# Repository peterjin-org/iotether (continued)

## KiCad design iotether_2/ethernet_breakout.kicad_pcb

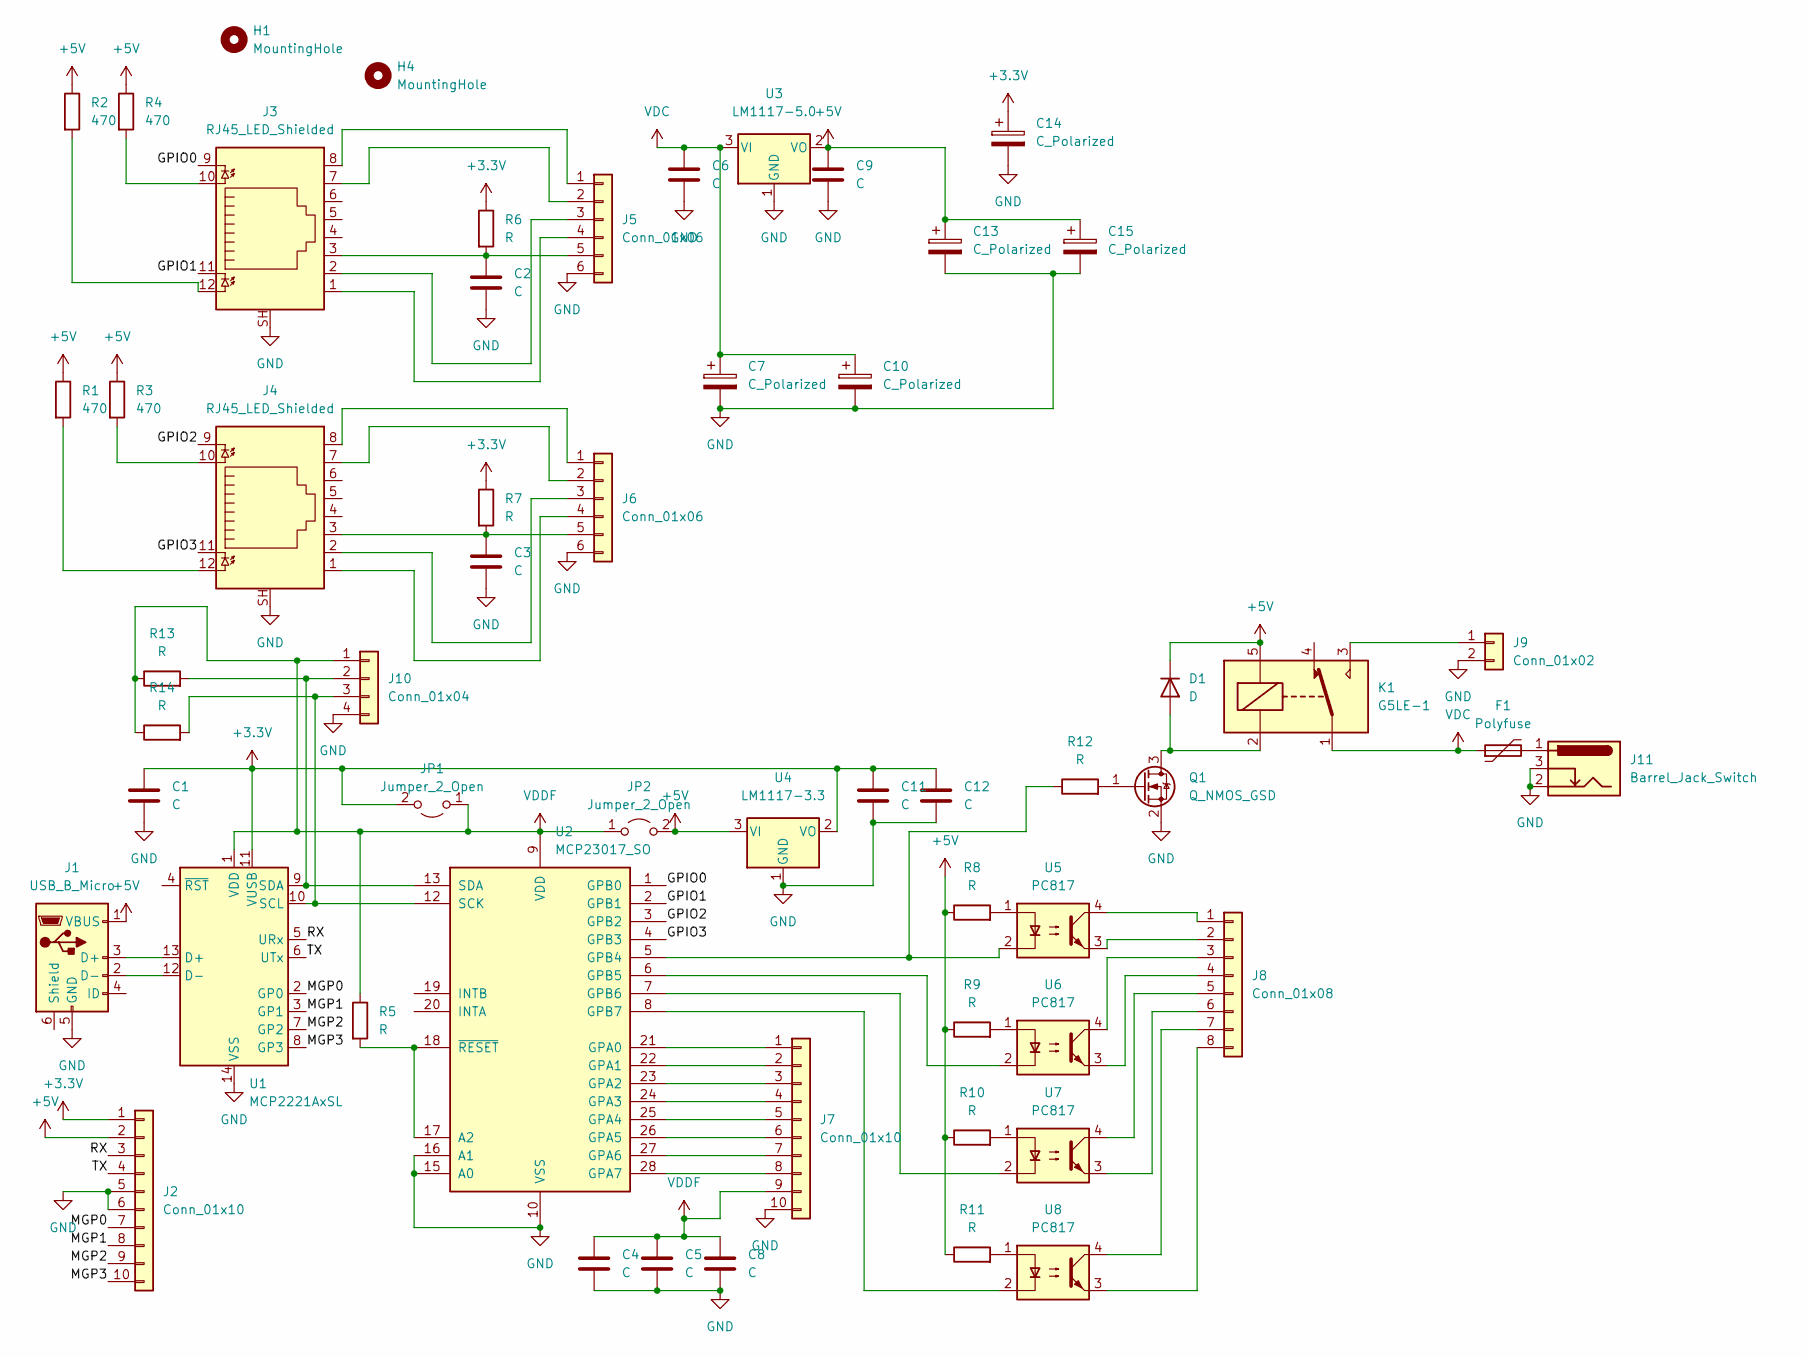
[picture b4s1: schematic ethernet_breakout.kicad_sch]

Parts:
C1, C2, C3, C4, C5, C6, C8, C9, C11, C12: C; C_0603_1608Metric_Pad1.08x0.95mm_HandSolder
C7, C10, C13, C14, C15: C_Polarized; CP_Radial_D8.0mm_P3.50mm
D1: D; D_DO-41_SOD81_P3.81mm_Vertical_AnodeUp
F1: Polyfuse; Fuse_Bourns_MF-RHT500
H1, H4: MountingHole; MountingHole_3.2mm_M3
J1: USB_B_Micro; PinHeader_1x06_P2.54mm_Vertical
J2, J7: Conn_01x10; PinHeader_1x10_P2.54mm_Vertical
J3, J4: RJ45_LED_Shielded; RJ45_Cetus_J1B1211CCD_Horizontal
J5, J6: Conn_01x06; PinHeader_1x06_P2.54mm_Vertical
J8: Conn_01x08; PinHeader_2x04_P2.54mm_Vertical
J9: Conn_01x02; TerminalBlock_bornier-2_P5.08mm
J10: Conn_01x04; PinHeader_1x04_P2.54mm_Vertical
J11: Barrel_Jack_Switch; BarrelJack_Horizontal
JP1, JP2: Jumper_2_Open; R_0603_1608Metric_Pad0.98x0.95mm_HandSolder
K1: G5LE-1; Relay_SPDT_Omron-G5LE-1
Q1: Q_NMOS_GSD; SOT-23-3
R1, R2, R3, R4: 470; R_0603_1608Metric
R5, R6, R7, R8, R9, R10, R11, R12, R13, R14: R; R_0603_1608Metric_Pad0.98x0.95mm_HandSolder
U1: MCP2221AxSL; SOIC-14_3.9x8.7mm_P1.27mm
U2: MCP23017_SO; SOIC-28W_7.5x17.9mm_P1.27mm
U3: LM1117-5.0; SOT-223-3_TabPin2
U4: LM1117-3.3; SOT-223-3_TabPin2
U5, U6, U7, U8: PC817; DIP-4_W7.62mm

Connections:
+3.3V: C1.1, C11.1, C12.1, C14.1, J2.1, JP1.2 (B), R6.1, R7.1, U1.11 (VUSB), U4.2 (VO)
+5V: C9.1, C13.1, C15.1, D1.1 (K), J1.1 (VBUS), J2.2, JP2.2 (B), K1.5, R1.1, R2.1, R3.1, R4.1, R8.1, R9.1, R10.1, R11.1, U3.2 (VO), U4.3 (VI)
/GPIO0: J3.9, U2.1 (GPB0)
/GPIO1: J3.11, U2.2 (GPB1)
/GPIO2: J4.9, U2.3 (GPB2)
/GPIO3: J4.11, U2.4 (GPB3)
/MGP0: J2.7, U1.2 (GP0)
/MGP1: J2.8, U1.3 (GP1)
/MGP2: J2.9, U1.7 (GP2)
/MGP3: J2.10, U1.8 (GP3)
/RX: J2.3, U1.5 (URx)
/TX: J2.4, U1.6 (UTx)
GND: C1.2, C2.2, C3.2, C4.2, C5.2, C6.2, C7.2, C8.2, C9.2, C10.2, C11.2, C12.2, C13.2, C14.2, C15.2, J1.5 (GND), J2.5, J2.6, J3.SH, J4.SH, J5.6, J6.6, J7.10, J9.2, J10.4, J11.2, J11.3, Q1.2 (S), U1.14 (VSS), U2.10 (VSS), U2.15 (A0), U2.16 (A1), U3.1 (GND), U4.1 (GND)
unnamed: C2.1, J3.3, J5.5, R6.2
unnamed: C3.1, J4.3, J6.5, R7.2
unnamed: D1.2 (A), K1.2, Q1.3 (D)
unnamed: J1.2 (D-), U1.12 (D-)
unnamed: J1.3 (D+), U1.13 (D+)
unnamed: J3.1, J5.4
unnamed: J3.2, J5.3
unnamed: J3.7, J5.2
unnamed: J3.8, J5.1
unnamed: J3.10, R4.2
unnamed: J3.12, R2.2
unnamed: J4.1, J6.4
unnamed: J4.2, J6.3
unnamed: J4.7, J6.2
unnamed: J4.8, J6.1
unnamed: J4.10, R3.2
unnamed: J4.12, R1.2
unnamed: J7.1, U2.21 (GPA0)
unnamed: J7.2, U2.22 (GPA1)
unnamed: J7.3, U2.23 (GPA2)
unnamed: J7.4, U2.24 (GPA3)
unnamed: J7.5, U2.25 (GPA4)
unnamed: J7.6, U2.26 (GPA5)
unnamed: J7.7, U2.27 (GPA6)
unnamed: J7.8, U2.28 (GPA7)
unnamed: J8.1, U5.4
unnamed: J8.2, U5.3
unnamed: J8.3, U6.4
unnamed: J8.4, U6.3
unnamed: J8.5, U7.4
unnamed: J8.6, U7.3
unnamed: J8.7, U8.4
unnamed: J8.8, U8.3
unnamed: J9.1, K1.3
unnamed: J10.2, R13.2, U1.9 (SDA), U2.13 (SDA)
unnamed: J10.3, R14.2, U1.10 (SCL), U2.12 (SCK)
unnamed: F1.2, J11.1
unnamed: Q1.1 (G), R12.2
unnamed: R5.2, U2.17 (A2), U2.18 (~RESET)
unnamed: R8.2, U5.1
unnamed: R9.2, U6.1
unnamed: R10.2, U7.1
unnamed: R11.2, U8.1
unnamed: R12.1, U2.5 (GPB4), U5.2
unnamed: U2.6 (GPB5), U6.2
unnamed: U2.7 (GPB6), U7.2
unnamed: U2.8 (GPB7), U8.2
VDC: C6.1, C7.1, C10.1, F1.1, K1.1, U3.3 (VI)
VDDF: C4.1, C5.1, C8.1, J7.9, J10.1, JP1.1 (A), JP2.1 (A), R5.1, R13.1, R14.1, U1.1 (VDD), U2.9 (VDD)

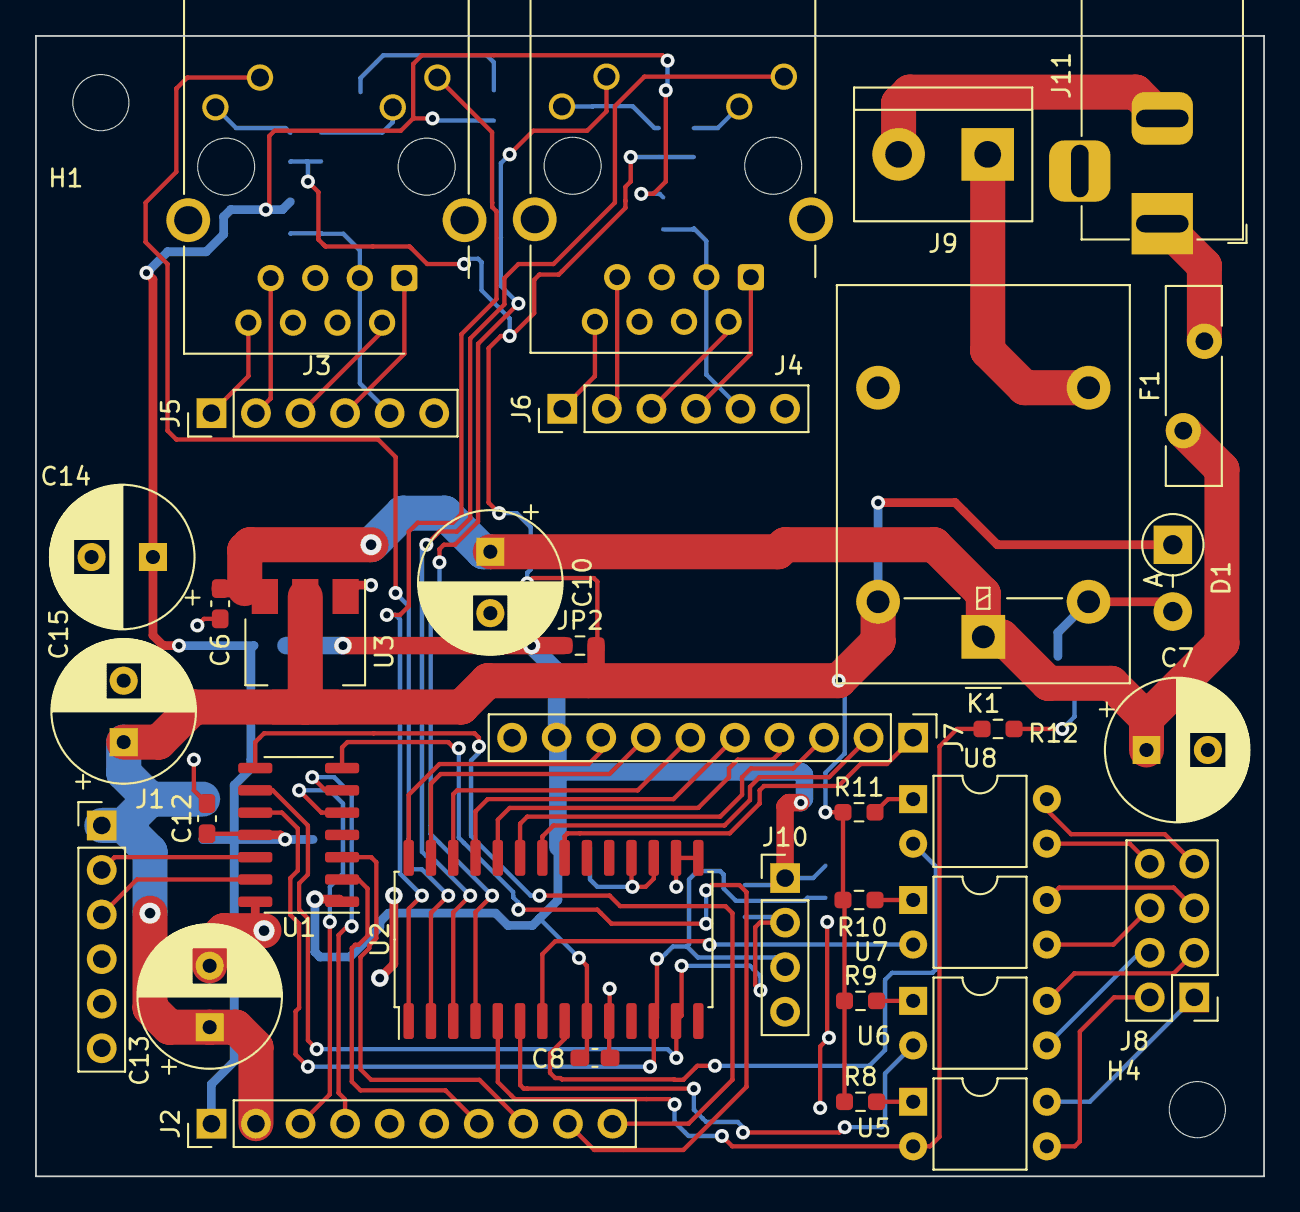
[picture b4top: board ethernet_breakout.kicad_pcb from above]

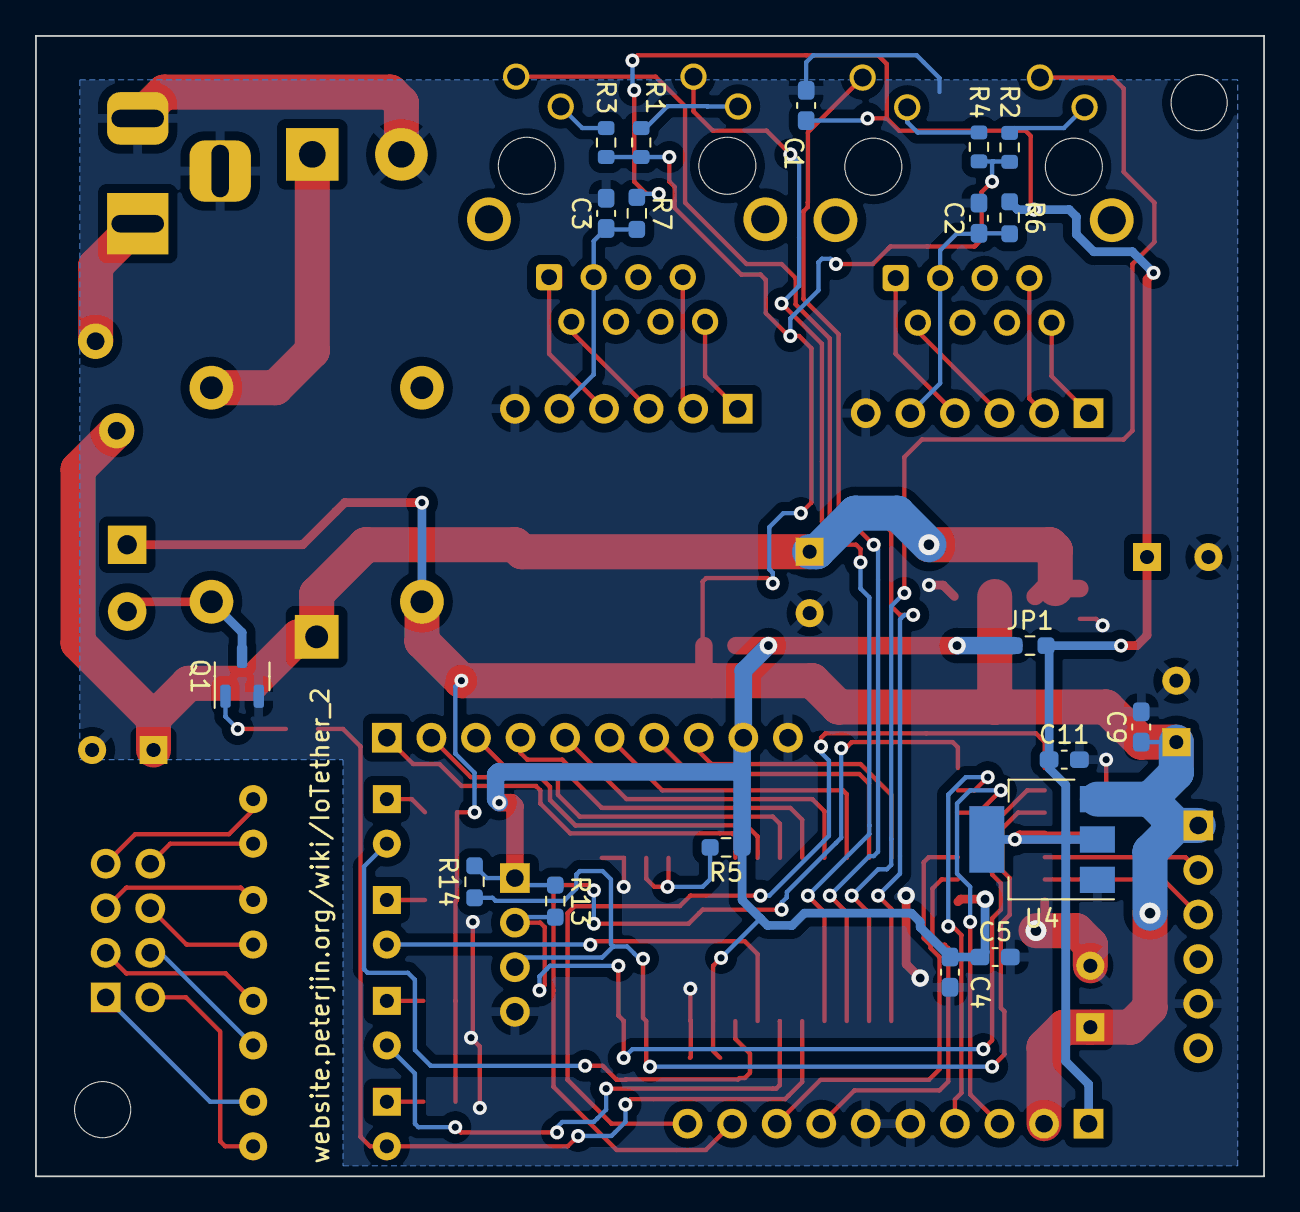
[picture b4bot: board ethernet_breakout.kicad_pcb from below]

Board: 2 copper layers, 70.0 x 65.0 mm, 56 parts (19 on the bottom side), 62 nets.

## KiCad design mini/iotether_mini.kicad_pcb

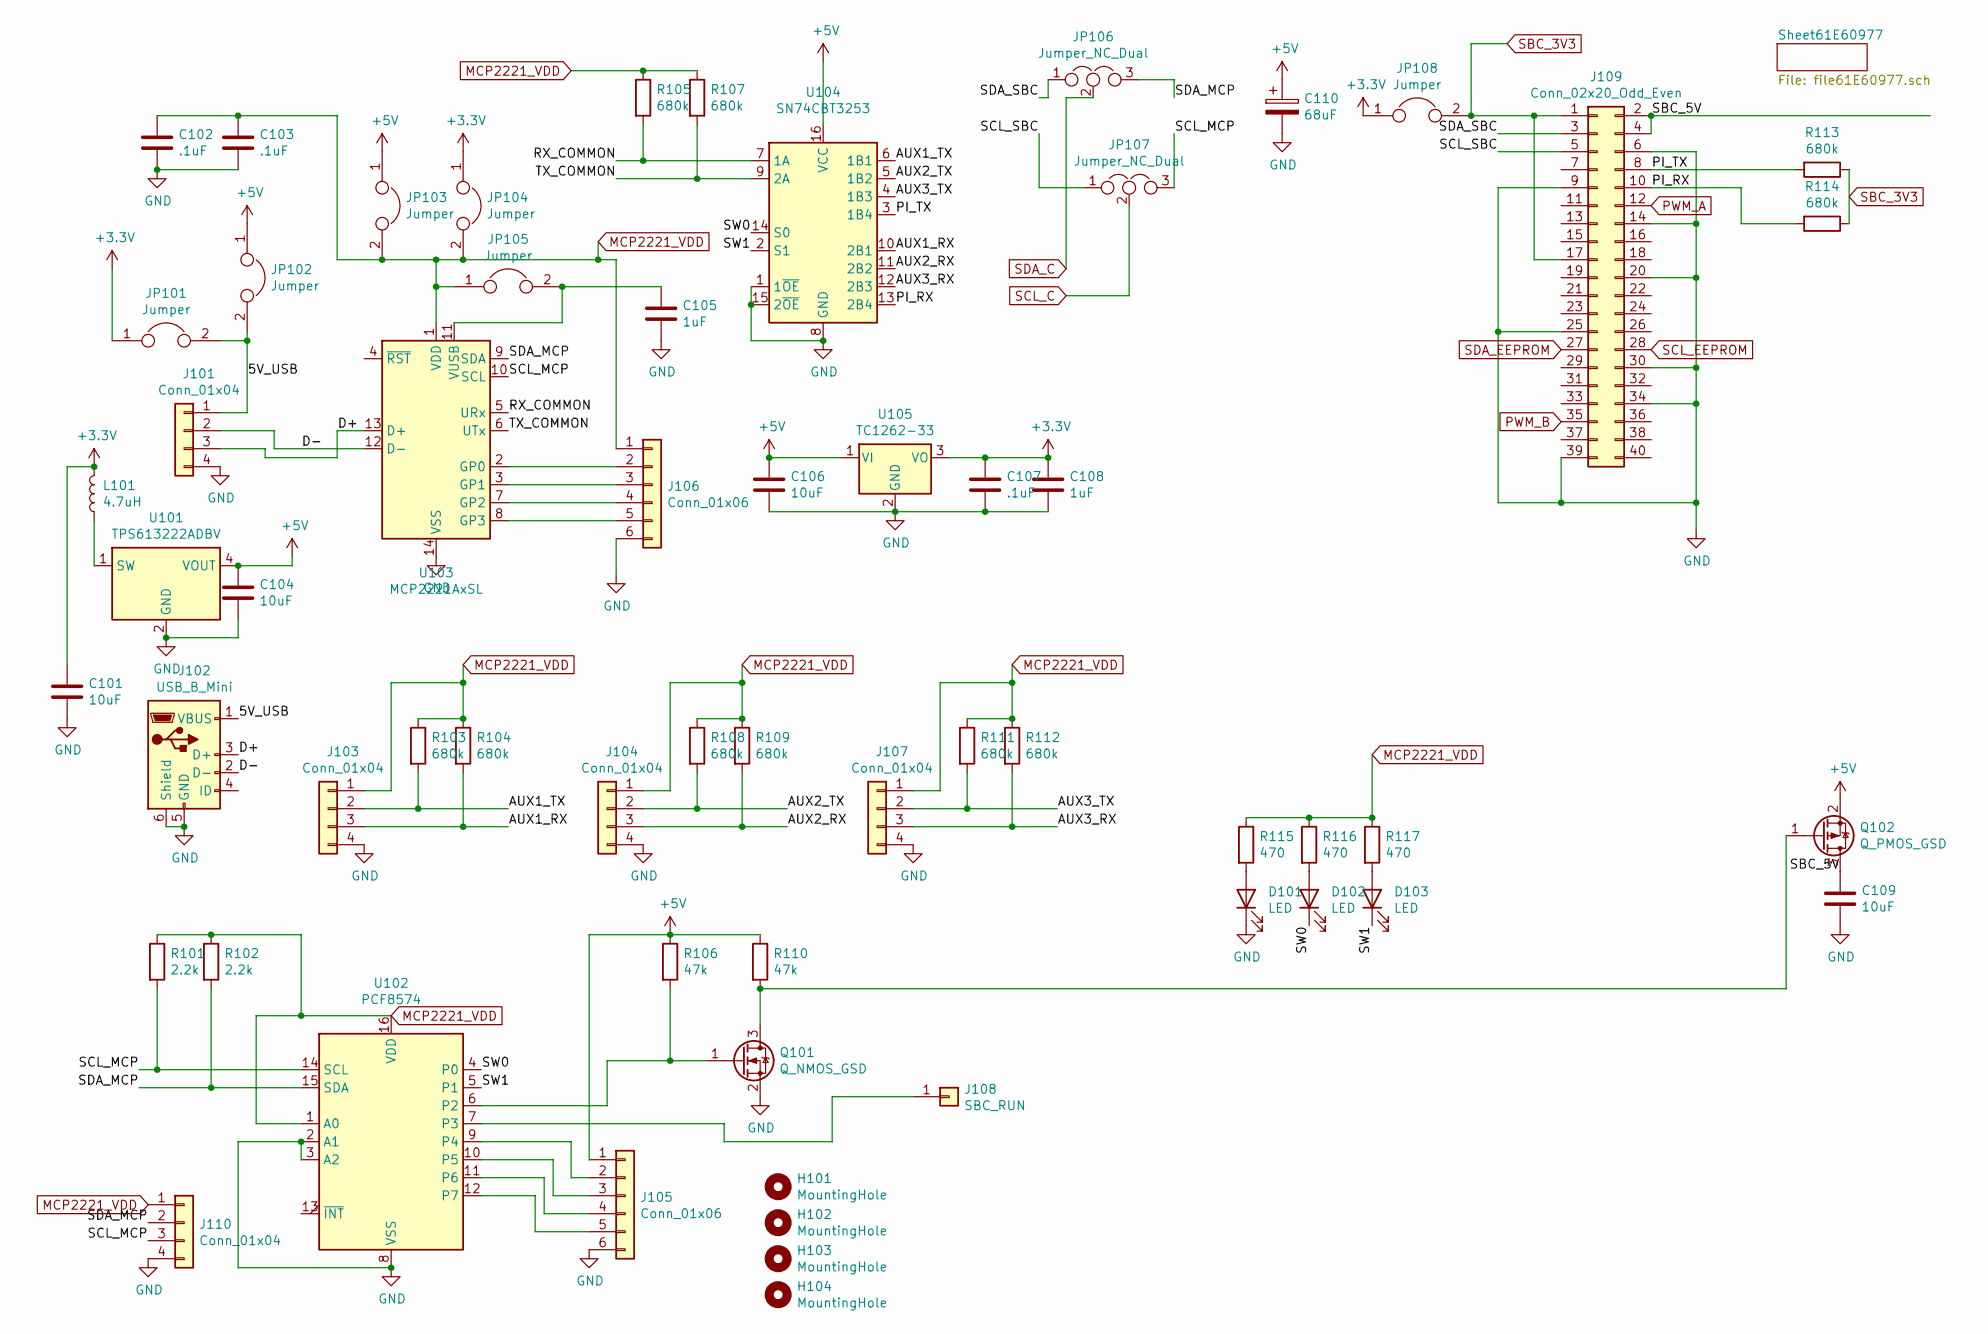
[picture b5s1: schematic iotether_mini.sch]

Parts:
C101, C104, C106, C109: 10uF; C_0805_2012Metric_Pad1.18x1.45mm_HandSolder
C102, C103, C107: .1uF; C_0603_1608Metric_Pad1.08x0.95mm_HandSolder
C105, C108: 1uF; C_0805_2012Metric_Pad1.18x1.45mm_HandSolder
C110: 68uF; CP_Radial_D8.0mm_P3.80mm
D101, D102, D103: LED; LED_0603_1608Metric_Pad1.05x0.95mm_HandSolder
H101, H102, H103, H104: MountingHole; MountingHole_2.7mm_M2.5
J101, J103, J104, J107, J110: Conn_01x04; PinHeader_1x04_P2.54mm_Vertical
J102: USB_B_Mini; USB_Mini-B_Wuerth_65100516121_Horizontal
J105, J106: Conn_01x06; PinHeader_1x06_P2.54mm_Vertical
J108: SBC_RUN; PinHeader_1x01_P2.54mm_Vertical
J109: Conn_02x20_Odd_Even; PinHeader_2x20_P2.54mm_Vertical
JP101, JP102, JP103, JP104, JP105, JP108: Jumper; R_0603_1608Metric
JP106, JP107: Jumper_NC_Dual; SOT-23
L101: 4.7uH; L_1210_3225Metric_Pad1.42x2.65mm_HandSolder
Q101: Q_NMOS_GSD; SOT-23
Q102: Q_PMOS_GSD; SOT-23
R101, R102: 2.2k; R_0603_1608Metric_Pad0.98x0.95mm_HandSolder
R103, R104, R105, R107, R108, R109, R111, R112, R113, R114: 680k; R_0603_1608Metric_Pad0.98x0.95mm_HandSolder
R106, R110: 47k; R_0603_1608Metric_Pad0.98x0.95mm_HandSolder
R115, R116, R117: 470; R_0603_1608Metric_Pad0.98x0.95mm_HandSolder
U101: TPS613222ADBV; SOT-23-5
U102: PCF8574; SOIC-16W_7.5x10.3mm_P1.27mm
U103: MCP2221AxSL; SOIC-14_3.9x8.7mm_P1.27mm
U104: SN74CBT3253; SOIC-16_3.9x9.9mm_P1.27mm
U105: TC1262-33; SOT-223-3_TabPin2

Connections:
+3V3: C101.1, C107.1, C108.1, JP101.1, JP104.1, JP108.1, L101.2, U105.3 (VO); also elsewhere on the board
+5V: C104.1, C106.1, C110.1, J105.1, JP102.1, JP103.1, Q102.2 (S), R106.1, R110.1, U101.4 (VOUT), U104.16 (VCC), U105.1 (VI); also elsewhere on the board
/5V_USB: J101.1, J102.1 (VBUS), JP101.2, JP102.2
/AUX1_RX: J103.3, R104.2, U104.10 (2B1)
/AUX1_TX: J103.2, R103.2, U104.6 (1B1)
/AUX2_RX: J104.3, R109.2, U104.11 (2B2)
/AUX2_TX: J104.2, R108.2, U104.5 (1B2)
/AUX3_RX: J107.3, R112.2, U104.12 (2B3)
/AUX3_TX: J107.2, R111.2, U104.4 (1B3)
/D+: J101.3, J102.3 (D+), U103.13 (D+)
/D-: J101.2, J102.2 (D-), U103.12 (D-)
/PI_RX: J109.10, R114.2, U104.13 (2B4)
/PI_TX: J109.8, R113.2, U104.3 (1B4)
/RX_COMMON: R105.2, U103.5 (URx), U104.7 (1A)
/SBC_5V: C109.1, J109.2, J109.4, Q102.3 (D)
/SCL_MCP: J110.3, JP107.3, R101.2, U102.14 (SCL), U103.10 (SCL)
/SCL_SBC: J109.5, JP107.1
/SDA_MCP: J110.2, JP106.3, R102.2, U102.15 (SDA), U103.9 (SDA)
/SDA_SBC: J109.3, JP106.1
/SW0: D102.1 (K), U102.4 (P0), U104.14 (S0)
/SW1: D103.1 (K), U102.5 (P1), U104.2 (S1)
/TX_COMMON: R107.2, U103.6 (UTx), U104.9 (2A)
GND: C101.2, C102.2, C103.2, C104.2, C105.2, C106.2, C107.2, C108.2, C109.2, C110.2, D101.1 (K), J101.4, J102.5 (GND), J102.6 (Shield), J103.4, J104.4, J105.6, J106.6, J107.4, J109.6, J109.9, J109.14, J109.20, J109.25, J109.30, J109.34, J109.39, J110.4, Q101.2 (S), U101.2 (GND), U102.2 (A1), U102.3 (A2), U102.8 (VSS), U103.14 (VSS), U104.1 (1~OE), U104.8 (GND), U104.15 (2~OE), U105.2 (GND); also elsewhere on the board
MCP2221_VDD: C102.1, C103.1, J103.1, J104.1, J106.1, J107.1, J110.1, JP103.2, JP104.2, JP105.1, R101.1, R102.1, R103.1, R104.1, R105.1, R107.1, R108.1, R109.1, R111.1, R112.1, R115.1, R116.1, R117.1, U102.1 (A0), U102.16 (VDD), U103.1 (VDD)
unnamed: C105.1, JP105.2, U103.11 (VUSB)
unnamed: D101.2 (A), R115.2
unnamed: D102.2 (A), R116.2
unnamed: D103.2 (A), R117.2
unnamed: J105.2, U102.9 (P4)
unnamed: J105.3, U102.10 (P5)
unnamed: J105.4, U102.11 (P6)
unnamed: J105.5, U102.12 (P7)
unnamed: J106.2, U103.2 (GP0)
unnamed: J106.3, U103.3 (GP1)
unnamed: J106.4, U103.7 (GP2)
unnamed: J106.5, U103.8 (GP3)
unnamed: J108.1, U102.7 (P3)
unnamed: L101.1, U101.1 (SW)
unnamed: Q101.1 (G), R106.2, U102.6 (P2)
unnamed: Q101.3 (D), Q102.1 (G), R110.2
PWM_A: J109.12; also elsewhere on the board
PWM_B: J109.35; also elsewhere on the board
SBC_3V3: J109.1, J109.17, JP108.2, R113.1, R114.1; also elsewhere on the board
SCL_C: JP107.2; also elsewhere on the board
SCL_EEPROM: J109.28; also elsewhere on the board
SDA_C: JP106.2; also elsewhere on the board
SDA_EEPROM: J109.27; also elsewhere on the board

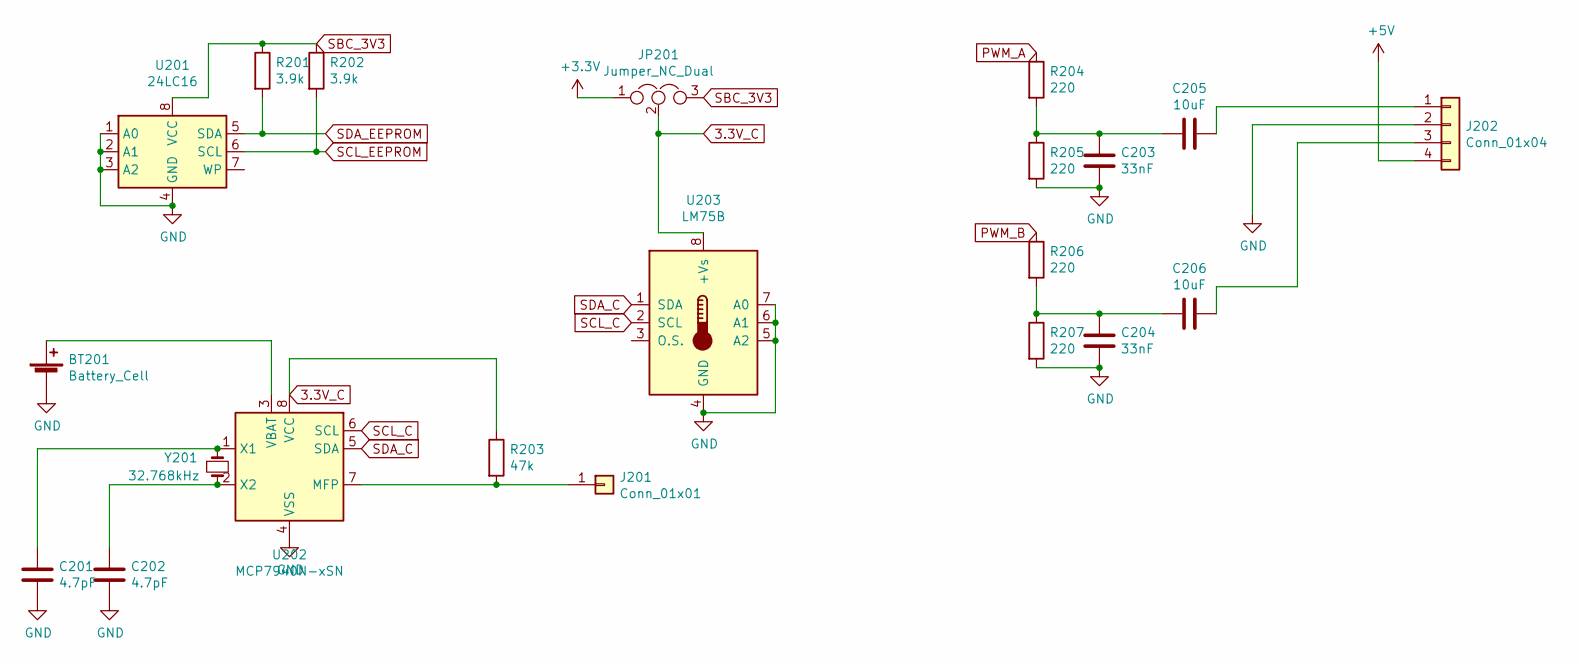
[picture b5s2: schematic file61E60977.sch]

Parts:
BT201: Battery_Cell; PinHeader_1x02_P2.54mm_Vertical
C201, C202: 4.7pF; C_0603_1608Metric_Pad1.08x0.95mm_HandSolder
C203, C204: 33nF; C_0603_1608Metric_Pad1.08x0.95mm_HandSolder
C205, C206: 10uF; C_0805_2012Metric_Pad1.18x1.45mm_HandSolder
J201: Conn_01x01; PinHeader_1x01_P2.54mm_Vertical
J202: Conn_01x04; PinHeader_1x04_P2.54mm_Vertical
JP201: Jumper_NC_Dual; SOT-23
R201, R202: 3.9k; R_0603_1608Metric_Pad0.98x0.95mm_HandSolder
R203: 47k; R_0603_1608Metric_Pad0.98x0.95mm_HandSolder
R204, R205, R206, R207: 220; R_0603_1608Metric_Pad0.98x0.95mm_HandSolder
U201: 24LC16; DIP-8_W7.62mm_Socket
U202: MCP7940N-xSN; SOIC-8_3.9x4.9mm_P1.27mm
U203: LM75B; SOIC-8_3.9x4.9mm_P1.27mm
Y201: 32.768kHz; Crystal_C26-LF_D2.1mm_L6.5mm_Horizontal

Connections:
3.3V_C: JP201.2, R203.1, U202.8 (VCC), U203.8 (+Vs)
+3V3: JP201.1; also elsewhere on the board
+5V: J202.4; also elsewhere on the board
GND: BT201.2 (-), C201.2, C202.2, C203.2, C204.2, J202.2, R205.2, R207.2, U201.1 (A0), U201.2 (A1), U201.3 (A2), U201.4 (GND), U202.4 (VSS), U203.4 (GND), U203.5 (A2), U203.6 (A1), U203.7 (A0); also elsewhere on the board
unnamed: BT201.1 (+), U202.3 (VBAT)
unnamed: C201.1, U202.1 (X1), Y201.1
unnamed: C202.1, U202.2 (X2), Y201.2
unnamed: C203.1, C205.2, R204.2, R205.1
unnamed: C204.1, C206.2, R206.2, R207.1
unnamed: C205.1, J202.1
unnamed: C206.1, J202.3
unnamed: J201.1, R203.2, U202.7 (MFP)
PWM_A: R204.1; also elsewhere on the board
PWM_B: R206.1; also elsewhere on the board
SBC_3V3: JP201.3, R201.1, R202.1, U201.8 (VCC); also elsewhere on the board
SCL_C: U202.6 (SCL), U203.2 (SCL); also elsewhere on the board
SCL_EEPROM: R202.2, U201.6 (SCL); also elsewhere on the board
SDA_C: U202.5 (SDA), U203.1 (SDA); also elsewhere on the board
SDA_EEPROM: R201.2, U201.5 (SDA); also elsewhere on the board

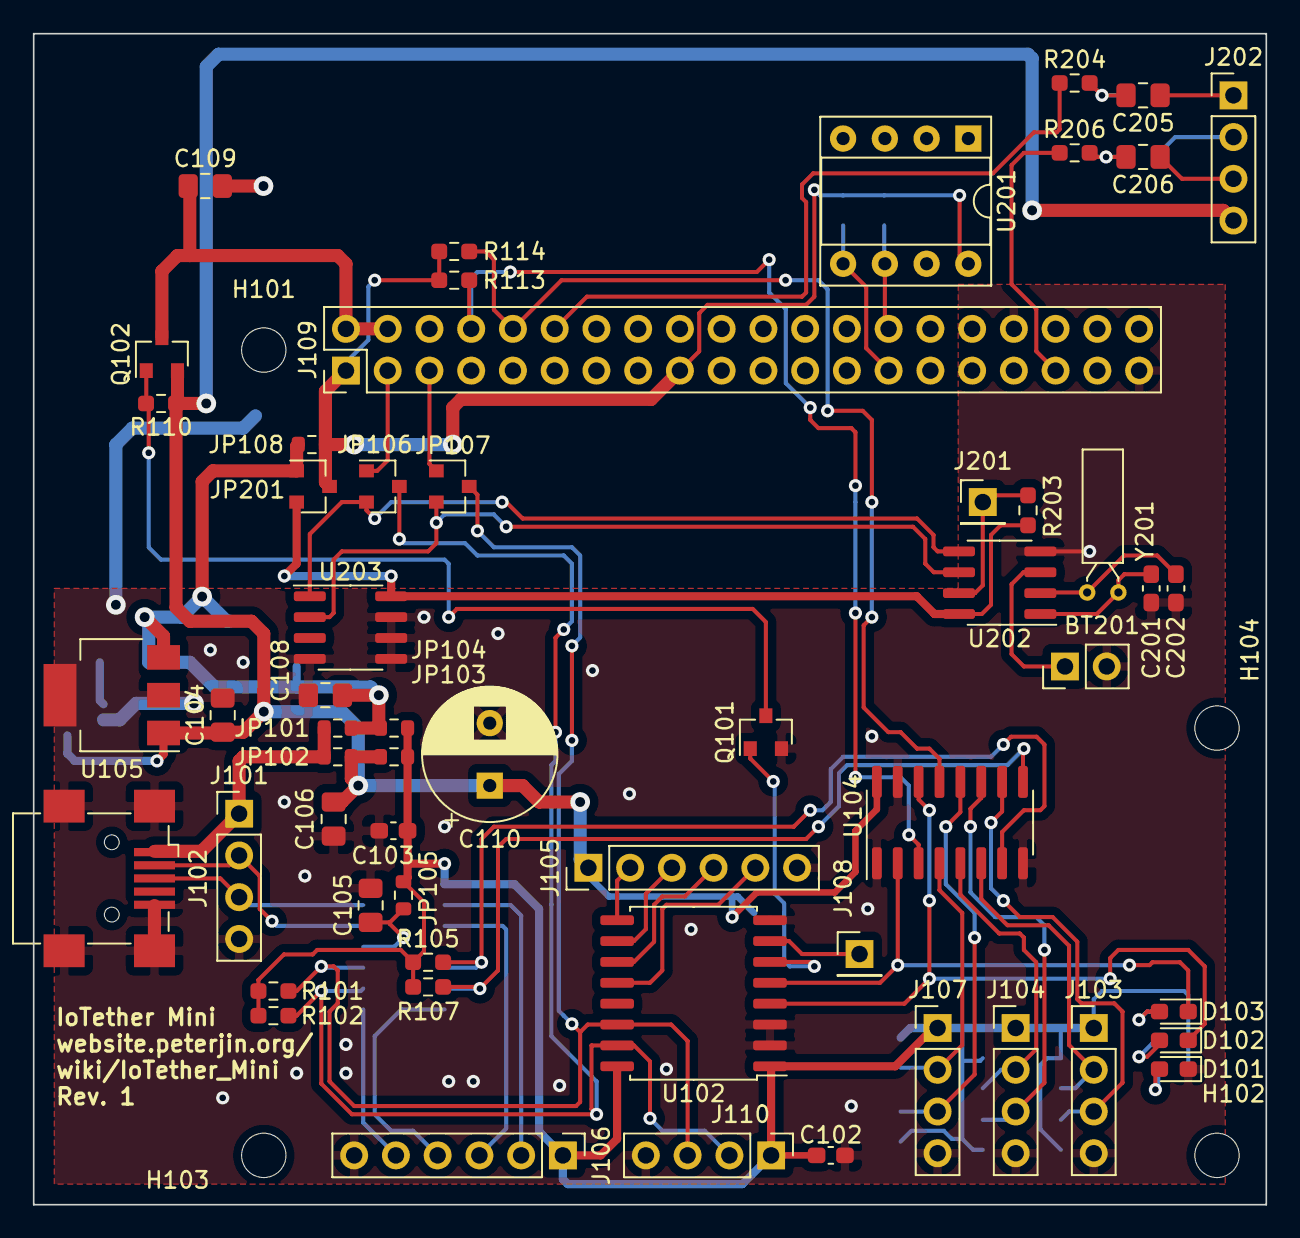
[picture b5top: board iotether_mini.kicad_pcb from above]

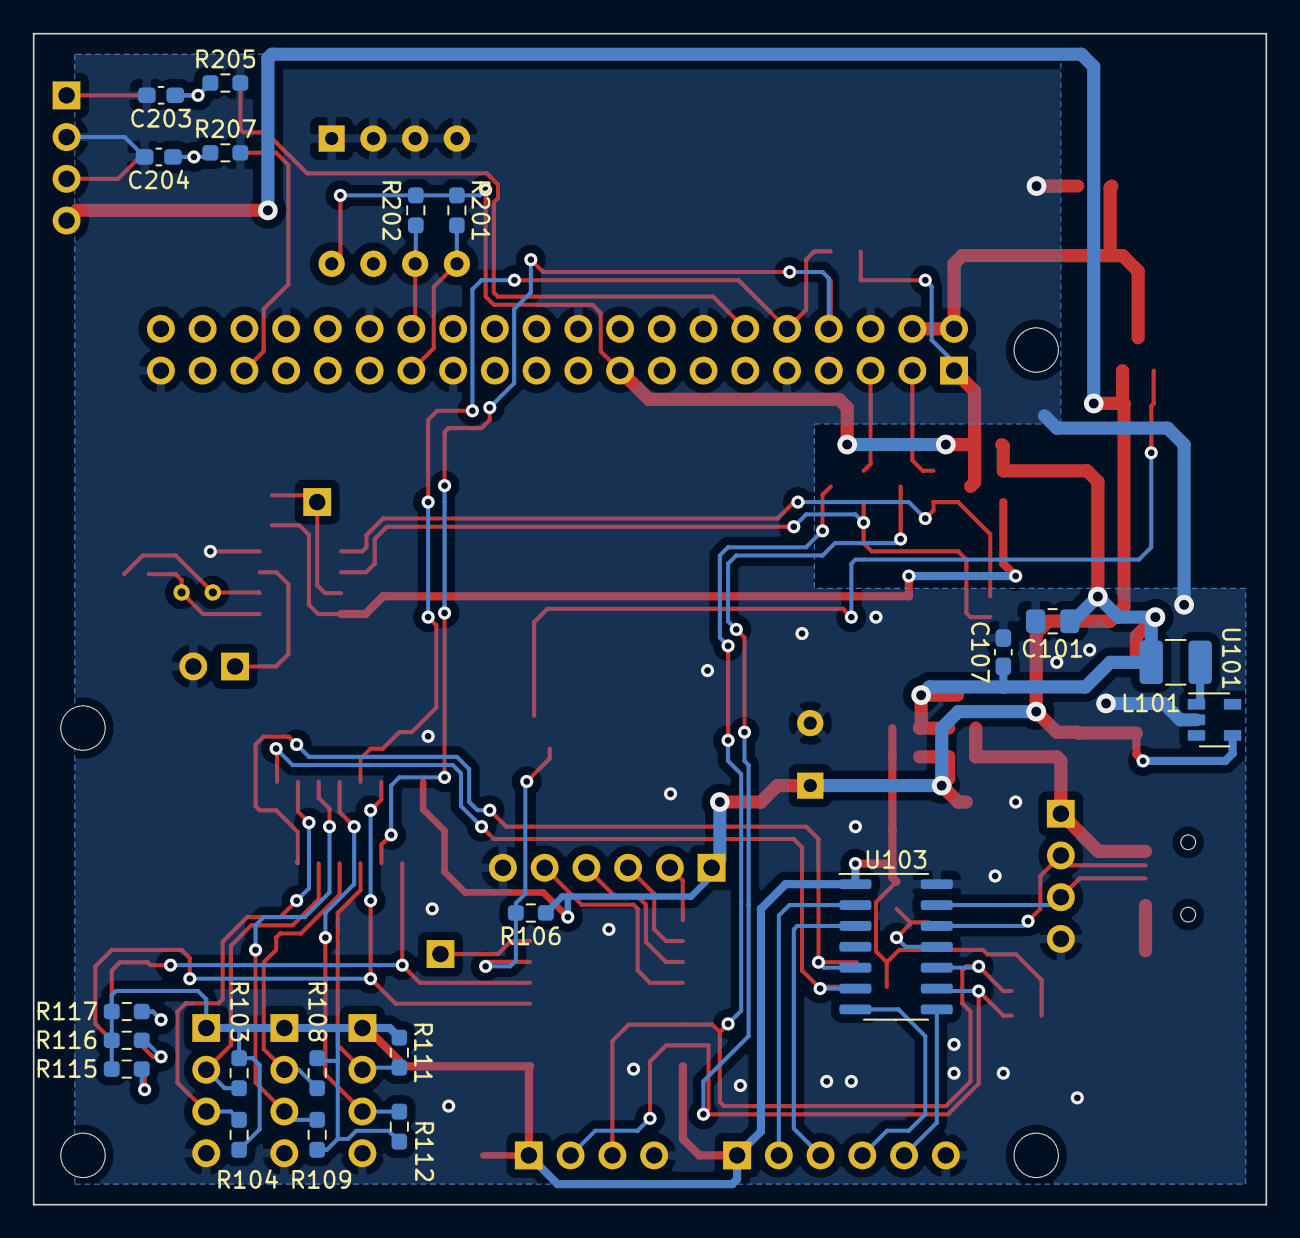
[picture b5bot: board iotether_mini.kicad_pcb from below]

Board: 2 copper layers, 75.0 x 71.2 mm, 81 parts (21 on the bottom side), 56 nets.

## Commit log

2021-12-13 Add LICENSE
2022-01-09 Clarify 'Software' in license to include hardware
2022-01-11 Revision 2
2022-01-11 Move U_MCP diff pair correction upwards
2022-01-11 DRC pass 0/0
2022-01-11 Fix again
2022-01-13 Add IoTether Mini
2022-01-14 Clarify license of open hardware logo
2023-12-26 Add IoTether 2, fix the USB on IoTether 1
2024-02-06 Add i2c_sampler, update to revision 3
2024-03-10 Add 12V->5V regulator
2025-02-10 Update I2C sampler and IoTether, add voltage converter
2025-03-16 IoTether: Add USB-C
2025-03-18 iotether
2025-08-01 Update IoTether and I2C sampler
